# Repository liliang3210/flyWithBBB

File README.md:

# flyWithBBB
extension board for Beaglebone black. add sensors to BBB to let it fly.

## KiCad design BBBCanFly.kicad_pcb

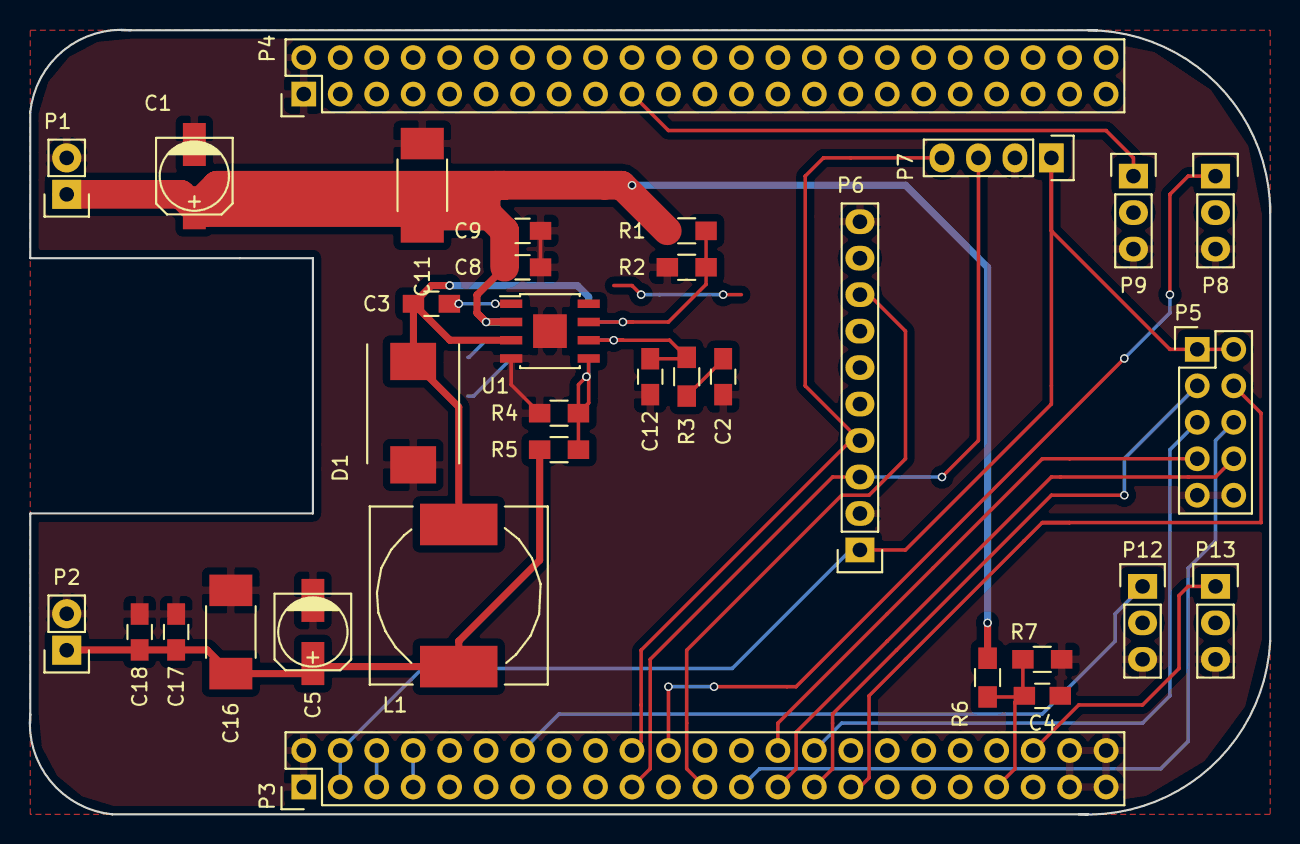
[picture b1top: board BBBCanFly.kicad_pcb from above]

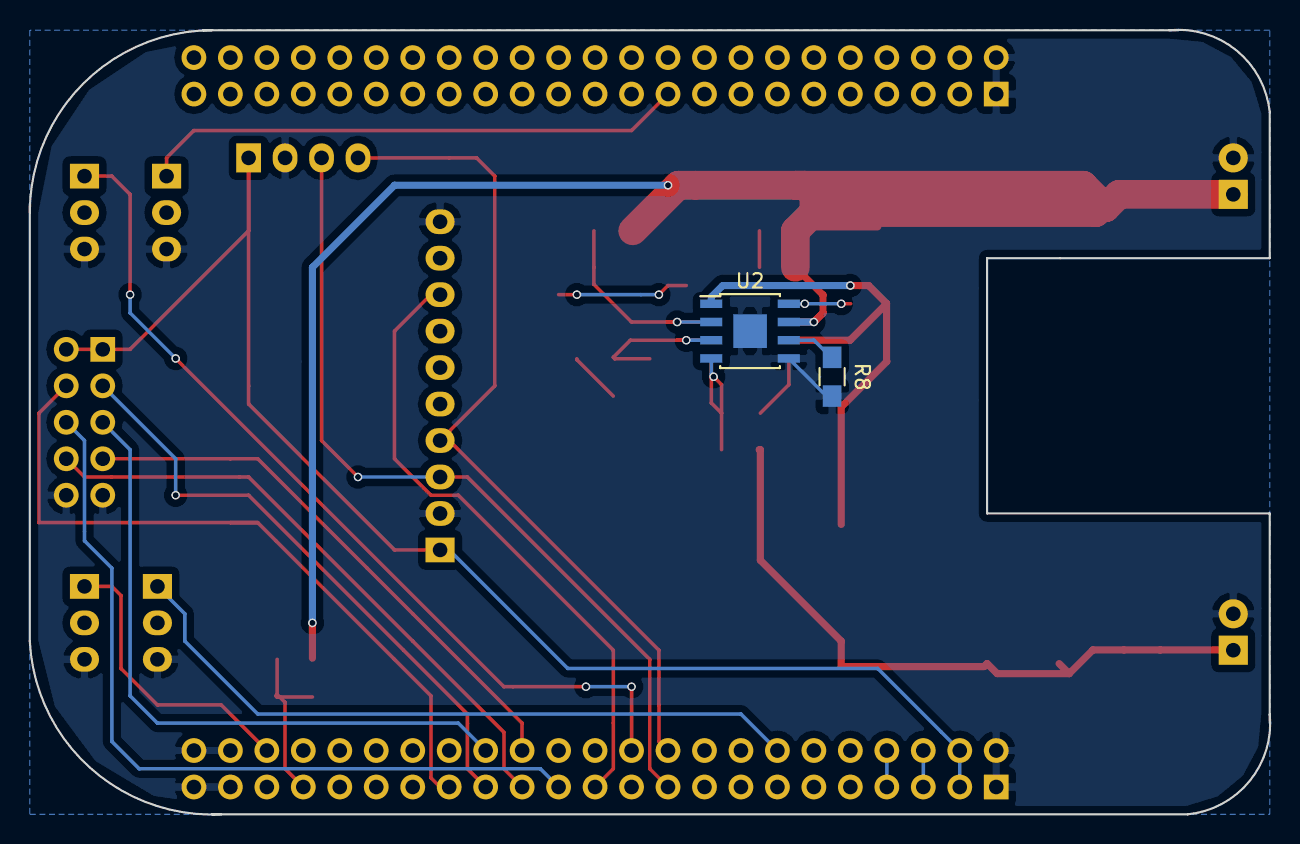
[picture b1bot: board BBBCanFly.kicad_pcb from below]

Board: 2 copper layers, 86.4 x 54.7 mm, 35 parts (2 on the bottom side), 27 nets.

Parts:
C1: 10u; c_elec_5x5.7
C2: 1.5n; C_0805_HandSoldering
C3: 10n; C_0805_HandSoldering
C4: 10p; C_0805_HandSoldering
C5: 22u; c_elec_5x5.7
C8, C9, C12, C17, C18: C; C_0805_HandSoldering
C11, C16: C; C_1812_HandSoldering
D1: B230A; DO-214AB
L1: 15uH; Neosid_Inductor_SM-NE127
P1: CONN_01X02; Pin_Header_Straight_1x02
P2: CONN_1x2; Pin_Header_Straight_1x02
P3, P4: CONN_02X23; Pin_Header_Straight_2x23
P5: CONN_02X05; Pin_Header_Straight_2x05
P6: CONN_10; Pin_Header_Straight_1x10
P7: CONN_4; Pin_Header_Straight_1x04
P8, P9, P12, P13: CONN_01X03; Pin_Header_Straight_1x03
R1: 100k; R_0805_HandSoldering
R2, R4: 10k; R_0805_HandSoldering
R3: 18k; R_0805_HandSoldering
R5: 47k; R_0805_HandSoldering
R6: 200K; R_0805_HandSoldering
R7: 30K; R_0805_HandSoldering
R8: 200k; R_0805_HandSoldering
U1: HT7465; SOIC-8-1EP_3.9x4.9mm_Pitch1.27mm
U2: MP1584EN; SOIC-8-1EP_3.9x4.9mm_Pitch1.27mm

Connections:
/interface/24V: C1.1, C8.1, C9.1, C11.1, P1.1, R1.1, R6.1, U1.2, U2.7
/interface/AIN0: C4.1, P3.39, R6.2, R7.1
/interface/ECAPPWM0: P3.42, P13.1
/interface/EHRPWM0A: P3.22, P8.1
/interface/EHRPWM1A: P3.14, P12.1
/interface/EHRPWM2A: P4.19, P9.1
/interface/GPIO_49: P3.23, P6.8
/interface/GPIO_115: P3.27, P5.8
/interface/GPIO_117: P3.25, P5.6
/interface/I2C2_SCL: P3.19, P6.3, P7.3
/interface/I2C2_SDA: P3.20, P6.4, P7.4
/interface/SPI1_CS0: P3.28, P5.7
/interface/SPI1_DI: P3.30, P5.5
/interface/SPI1_DO: P3.29, P5.3
/interface/SPI1_SCLK: P3.31, P5.4
/interface/SYS_5V: P3.7, P3.8
/interface/VDD_3V3: P3.3, P3.4, P5.1, P5.2, P6.1, P7.1
/interface/VDD_5V: P3.5, P3.6
/power/BST: C3.2, U1.1, U2.8
/power/COMP: C12.1, R3.1, U1.6, U2.3
/power/EN: R1.2, R2.1, U1.7, U2.2
/power/FB: R4.1, R5.2, U1.5, U2.4
/power/SW: C3.1, D1.1, L1.2, U1.3, U2.1
/power/output: C5.1, C16.1, C17.1, C18.1, L1.1, P2.1, R5.1
GND: C1.2, C2.2, C4.2, C5.2, C8.2, C9.2, C11.2, C12.2, C16.2, C17.2, C18.2, D1.2, P1.2, P2.2, P3.1, P3.2, P3.43, P3.44, P3.45, P3.46, P4.1, P4.2, P5.9, P5.10, P6.2, P6.10, P7.2, P8.3, P9.3, P12.3, P13.3, R2.2, R4.2, R7.2, R8.2, U1.4, U1.9, U2.5, U2.9
unnamed: C2.1, R3.2
unnamed: R8.1, U2.6

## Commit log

2016-07-23 project init
2016-08-15 sch has been finished
2016-12-12 pcb finished.
2017-02-19 modified power supply program
2017-03-20 Set theme jekyll-theme-cayman
2017-07-16 latest version
